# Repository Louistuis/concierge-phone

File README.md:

# Concierge phone

A small candybar phone you click and talk to. It sends your voice to an AI concierge in the cloud and talks back, and it carries a whole toolbox of radios and sensors the concierge can use.

**Status: paused, not built, not tested.** Board 1.3 is fully placed and passes every check except routing: the auto-router (Quilter) failed on all three runs, so the copper traces are not drawn yet. Treat everything here as an untested design. The cost to build 2 is in [pcb/QUOTE.md](pcb/QUOTE.md).

## What's inside

| | |
|---|---|
| Body | 54 x 108 x 15.5 mm, natural aluminium, black glass front |
| Brain | Waveshare ESP32-P4-Module (ESP32-P4 + ESP32-C6 for Wi-Fi 6 and Bluetooth LE) |
| Screen | 1.8" AMOLED with touch |
| Mobile data | Quectel EG915U-EU LTE Cat-1bis, nano-SIM |
| Location | u-blox MAX-M10S GNSS |
| Voice | 2 MEMS mics, MAX98357A amp + speaker, fingerprint Talk key |
| Camera | OV5647, 5 MP |
| Radios | NFC (ST25R3916B), sub-GHz (CC1101), LoRa (SX1262), IR receiver |
| Sensors | air quality (SGP41), colour (AS7341), distance (VL53L1), pressure (BMP581), temperature and humidity (SHT40), motion (ICM-42670), light (OPT3004), compass (MMC5603) |
| Feel | LRA haptics (DRV2605L), 3 side keys, privacy slide switch |
| Power | 2400 mAh LiPo, BQ24074 charger, BQ27441 fuel gauge, USB-C |
| Storage | microSD |
| Board | 50 x 102 mm, 6 layers, 1.0 mm, JLCPCB JLC06101H-3313 stackup |

The board is designed so it goes together with no soldering: the screen, battery, camera, fingerprint reader, antennas and speaker plug in or press onto spring contacts, and the rest is screws.

## How it's made

The whole board is generated by Python scripts that run inside KiCad 10. Nothing is drawn by hand, so every change is a script edit and a re-run.

```
pcb/sch_*.py        netlists for each block (core, power, rf, sense, ui), every part with its datasheet notes
pcb/gen_*.py        footprints KiCad doesn't ship
pcb/make_board.py   builds and places the board
pcb/fit_check.py    3D check that every part fits under the screen, battery and case
pcb/route.py        net classes, impedance widths, export for routing
pcb/quilter_prep.py input files for the Quilter auto-router
pcb/order_check.py  the order gate: DRC, nets, parts stock, fit; prints READY TO ORDER or NOT READY
enclosure/          Blender scripts for the concept renders
research/           part research notes
DESIGN.md           every design decision, in order, with the reasons
```

Run them with KiCad's own Python:

```
KPY=/Applications/KiCad/KiCad.app/Contents/Frameworks/Python.framework/Versions/Current/bin/python3
cd pcb
$KPY make_board.py
$KPY check_nets.py
$KPY export_view.py > shots/board.json
$KPY fit_check.py
$KPY route.py export
$KPY quilter_prep.py
$KPY order_check.py quilter/A-route-only/phone.kicad_pcb 5
```

## Not included

Manufacturer datasheets aren't in this repo; each part's notes in `pcb/sch_*.py` name the document and page they came from. The firmware isn't written yet.

## License

MIT, see [LICENSE](LICENSE). Use it, change it, build it. If you build one, say hi.

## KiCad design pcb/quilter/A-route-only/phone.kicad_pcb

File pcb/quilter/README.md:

# Quilter upload (made by pcb/quilter_prep.py, 2026-11-13)

Upload the **three files** of one folder (no zip): `phone.kicad_pro`, `phone.kicad_sch`, `phone.kicad_pcb`.

| Folder | What Quilter does |
|---|---|
| `B-place-and-route/` (try first) | Places 368 parts itself and routes. 71 parts stay where the case needs them (antennas, keys, connectors, module, modem, Talk ring, antenna feeds, test pads under the battery). Keep-outs stop parts landing under the battery, the fingerprint button, the camera head and the antenna band. |
| `A-route-only/` (backup) | Every part stays where make_board.py put it; Quilter only routes. Same parts, so it can be a second job in the same project. |

Both pass KiCad schematic parity (0 issues). Left-over DRC items are inside the parts' own footprints (mic sound holes, SIM tray NPTH, SW74 pads at the edge) or the deliberately tight antenna pi-match chains.

## Job settings
1. Stackup: JLCPCB 6-layer (or "from input file": In1 = gnd, In4 = pwr).
2. Differential pairs: CSI_* pairs **100 ohm**; USB_DP/DN, USB_HS_DP/DN, USB_JTAG_DP/DN **85 ohm** (USB wants 90, Quilter offers 85 or 100).
3. Single-ended impedance: add by net class **RF50**, 50 ohm.
4. Power nets: net class **Power** (auto-detected).
5. Preserved pours: none.

Free (Non-Commercial) tier: Quilter's terms allow training on what is uploaded. Projects expire.
Download the best candidate as KiCad and put it in `pcb/quilter/result/`; then run DRC, check_nets.py and jlc_files.py on it.

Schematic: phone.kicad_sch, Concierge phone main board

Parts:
AE30: 0868AT43A0020E; Johanson_0868AT43A0020; LCSC C3284550
AE31: W3011; Pulse_W3011; LCSC C6604735
C1, C395: 22uF; C_0805_2012Metric; LCSC C45783
C2, C20, C24, C103, C104, C105, C108, C109, C130, C348, C374, C390, C392, C701, C712, C719: 10uF; C_0603_1608Metric; LCSC C19702
C3, C8, C11, C12, C13, C14, C18, C22, C23, C25, C26, C27, C110, C117, C120, C122, C124, C126, C131, C300, C331, C339, C340, C341, C342, C343, C344, C345, C346, C347, C355, C369, C372, C373, C387, C388, C393, C394, C500, C501, C502, C503, C504, C508, C509, C510, C511, C512, C517, C518, C700, C702, C703, C704, C705, C706, C707, C708, C710, C713, C716, C720: 100nF; C_0201_0603Metric; LCSC C1525
C4, C7, C21, C101, C121, C123, C125, C127, C128, C313, C513, C514, C515, C516, C709, C711, C714, C715, C717, C718: 1uF; C_0402_1005Metric; LCSC C52923
C5, C6, C9, C10: DNP 33pF; C_0402_1005Metric; not fitted
C15, C16, C17, C19, C118, C315, C316: 33pF; C_0201_0603Metric; LCSC C1562
C100: 100nF 50V; C_0603_1608Metric; LCSC C14663
C102: 4.7uF 25V; C_0603_1608Metric; LCSC C69335
C106, C107: 22uF; C_0603_1608Metric; LCSC C59461
C111, C112, C113: 22uF 0805; C_0805_2012Metric; LCSC C45783
C114, C115, C116: 100uF; C_1210_3225Metric; LCSC C49066
C119: 10pF; C_0201_0603Metric; LCSC C32949
C129: 0.47uF; C_0402_1005Metric; LCSC C92361
C132, C302, C304, C306, C308, C310, C314, C506: 10nF; C_0201_0603Metric; LCSC C15195
C301, C305, C307, C309, C505, C507: 2.2uF; C_0402_1005Metric; LCSC C12530
C303, C391, C519: 4.7uF; C_0402_1005Metric; LCSC C23733
C311: 22nF; C_0201_0603Metric; LCSC C1532
C312, C351, C352, C386: 1nF; C_0201_0603Metric; LCSC C1523
C317, C324: 680pF; C_0402_1005Metric; LCSC C301953
C318, C325, C364: 100pF; C_0402_1005Metric; LCSC C1546
C319, C326: DNP 10pF; C_0402_1005Metric; not fitted
C320, C327: 82pF; C_0402_1005Metric; LCSC C45501
C321, C328: 56pF; C_0402_1005Metric; LCSC C1572
C322, C329: 10pF; C_0402_1005Metric; LCSC C1545
C323, C330: 180pF; C_0402_1005Metric; LCSC C97862
C332: 3.9nF C0G 50V; C_0603_1608Metric; LCSC C415537
C333: 150pF C0G 50V; C_0603_1608Metric; LCSC C1645
C334: DNP 220pF C0G 50V; C_0603_1608Metric; not fitted
C335, C357, C361: 220pF; C_0402_1005Metric; LCSC C39122
C336: 1nF C0G; C_0402_1005Metric; LCSC C53547
C337: 2.2nF C0G; C_0402_1005Metric; LCSC C385029
C338: 1nF C0G; C_0201_0603Metric; LCSC C53547
C349, C350: 15pF; C_0201_0603Metric; LCSC C1548
C353, C354: 100pF; C_0201_0603Metric; LCSC C1546
C356, C358: 3.9pF; C_0402_1005Metric; LCSC C1566
C359: 8.2pF; C_0402_1005Metric; LCSC C1579
C360: 5.6pF; C_0402_1005Metric; LCSC C1574
C362: 1.0pF; C_0402_1005Metric; LCSC C1550
C363, C365: 1.5pF; C_0402_1005Metric; LCSC C1552
C366: 3.3pF; C_0402_1005Metric; LCSC C1565
C367: 12pF; C_0402_1005Metric; LCSC C1547
C368: DNP 47pF; C_0402_1005Metric; not fitted
C370: DNP 3.9pF; C_0402_1005Metric; not fitted
C371: DNP 0.3pF; C_0402_1005Metric; not fitted
C375: 470nF; C_0402_1005Metric; LCSC C5137475
C376: 47nF; C_0201_0603Metric; LCSC C82219
C377: 82pF; C_0201_0603Metric; LCSC C45501
C378, C380: 6.8pF; C_0402_1005Metric; LCSC C1576
C379, C384: 2.4pF; C_0402_1005Metric; LCSC C48346
C381: 47pF; C_0402_1005Metric; LCSC C1567
C382: 2.7pF; C_0402_1005Metric; LCSC C1561
C383: 1.8pF; C_0402_1005Metric; LCSC C1553
C385, C397: DNP 1.0pF; C_0402_1005Metric; not fitted
C389: 10pF; C_0201_0603Metric; LCSC C1545
C396: DNP 2.2pF; C_0402_1005Metric; not fitted
D100: SMF15A; D_SOD-123F; LCSC C123802
D101: PTVSHC3D4V5U; D_SOD-323; LCSC C319211
D102: XL-3030UWC-1W-3V; LED_XINGLIGHT_XL-3030_3.0x3.0mm; LCSC C2843891
D300, D301, D302: BAT54WS; D_SOD-323; LCSC C124205
D303, D304: IR12-21C/TR8; Everlight_IR12-21C; LCSC C53672
D700, D701, D702, D703: XL-1615RGBC-RF; LED_XINGLIGHT_XL-1615RGBC_1.6x1.5mm; LCSC C965840
F100: 1206L200/24NR 2A 24V; Fuse_1206_3216Metric; LCSC C42396578
J1: AXE534127; Panasonic_AXE534127_A4S_34P; LCSC C6863072
J2: NANO SIM 7P H1.37; SIM_Nano_SHOUHAN_7P_H1.37; LCSC C7529384
J3: AFA07-S15FCA-00; JUSHUO_AFA07-S15FCA-00_1x15-1MP_P1.0mm_Horizontal; LCSC C262721
J4: TYPE-C-31-M-12; USB_C_Receptacle_HRO_TYPE-C-31-M-12; LCSC C165948
J5: U.FL-R-SMT-1(10) LTE; U.FL_Hirose_U.FL-R-SMT-1_Vertical; LCSC C88373
J6: U.FL-R-SMT-1(10) Wi-Fi; U.FL_Hirose_U.FL-R-SMT-1_Vertical; LCSC C88373
J10: S3B-PH-SM4-TB(LF)(SN); JST_PH_S3B-PH-SM4-TB_1x03-1MP_P2.00mm_Horizontal; LCSC C265101
J30, J35: BWCD-L5.5W2.0H3.0; Pogo_KTR47003_D2.0; LCSC C2826550
J31: 4308RV-404XJL; Coilcraft_4308RV
J32: TP CC_GDO2; TestPoint_Pad_D1.0mm
J33: TP GNSS_TP; TestPoint_Pad_D1.0mm
J34: TP GNSS_SAFEBOOT; TestPoint_Pad_D1.0mm
J70: Molex 53261-0671; Molex_PicoBlade_53261-0671_1x06-1MP_P1.25mm_Horizontal; LCSC C17393620
J71: 104031-0811; microSD_HC_Molex_104031-0811; LCSC C585350
L100: DFE201612E-R47M=P2 0.47uH 5.5A; L_Murata_DFE201610P; LCSC C668312
L101: XFL4020-152MEC 1.5uH; L_Coilcraft_XxL4020; LCSC C3033018
L300, L301: 270nH; L_0805_2012Metric; LCSC C162661
L302, L303, L305: 27nH; L_0402_1005Metric; LCSC C12669
L304: 22nH; L_0402_1005Metric; LCSC C12670
L306, L307, L310, L311: 12nH; L_0402_1005Metric; LCSC C77104
L308, L309: 18nH; L_0402_1005Metric; LCSC C86060
L312: DNP 3.3nH; L_0402_1005Metric; not fitted
L313: 15uH; L_0603_1608Metric; LCSC C486329
L314: 47nH; L_0402_1005Metric; LCSC C97998
L315: 2.2nH; L_0402_1005Metric; LCSC C86061
L316: 3.3nH; L_0402_1005Metric; LCSC C86064
L317: 10nH; L_0402_1005Metric; LCSC C77103
L318: 15nH; L_0402_1005Metric; LCSC C86059
L319: FB600; L_0402_1005Metric; LCSC C76884
LS70: Same Sky CMS-16093-078S; SPK_SPRING_PADS_2P_P2.4mm
M70: GT-BTP20002-0170B-020A (LRA VG0832009L); GSwitch_GT-BTP20002-0170B_2P_P2.0; LCSC C55079717
Q1: 2N7002; SOT-23; LCSC C8545
Q100, Q300, Q301: DMG1012T-7; SOT-523; LCSC C20512
R1, R4, R11, R12, R14, R16, R102, R105, R106, R113, R123, R124, R307, R500, R501, R507, R703, R707, R708, R709, R710, R712, R720, R722, R723, R724, R725, R726: 10k; R_0201_0603Metric; LCSC C25744
R2, R3: 2.2k; R_0201_0603Metric; LCSC C25879
R5, R6: 0; R_0201_0603Metric; LCSC C17168
R7, R8, R9: 22; R_0201_0603Metric; LCSC C25092
R10: 51k; R_0201_0603Metric; LCSC C25794
R13, R15: DNP 10k; R_0402_1005Metric; not fitted
R17, R18, R717, R718: 100; R_0201_0603Metric; LCSC C25076
R19: 15k; R_0201_0603Metric; LCSC C25756
R103: 1.18k; R_0402_1005Metric; LCSC C270651
R104: 887; R_0402_1005Metric; LCSC C474137
R107: 10k; R_0201_0603Metric
R108: 511k; R_0201_0603Metric; LCSC C64042
R109: 91k; R_0201_0603Metric; LCSC C4147
R110: 10; R_0201_0603Metric; LCSC C25077
R111: 1.2M; R_0201_0603Metric; LCSC C43675
R112: 180k; R_0201_0603Metric; LCSC C25760
R114: 60.4k; R_0201_0603Metric; LCSC C25911
R115, R117, R119, R121, R126, R127, R305, R308, R310, R312, R314, R316, R320, R324, R328, R502, R503, R504, R505, R700, R711, R713, R714, R716, R719: 100k; R_0201_0603Metric; LCSC C25741
R116, R120: 75k; R_0201_0603Metric; LCSC C25798
R118: 39k; R_0201_0603Metric; LCSC C25783
R122: 10mR 1% 0.5W; R_0805_2012Metric; LCSC C163089
R125: 910k; R_0201_0603Metric; LCSC C25800
R300, R301: 2.4R; R_0603_1608Metric; LCSC C22941
R302, R303: 68R; R_0402_1005Metric; LCSC C25131
R304, R327: 0R; R_0201_0603Metric; LCSC C17168
R306: 10k; R_0402_1005Metric; LCSC C25744
R309, R318, R323, R325: 100R; R_0201_0603Metric; LCSC C25076
R311: 56k; R_0201_0603Metric; LCSC C25796
R313, R315, R701, R702, R706: 1k; R_0201_0603Metric; LCSC C11702
R317, R326: 0R; R_0402_1005Metric; LCSC C17168
R319: 220R; R_0201_0603Metric; LCSC C25091
R321, R322: 47R; R_0603_1608Metric; LCSC C23182
R506: 4.7; R_0201_0603Metric; LCSC C137962
R704, R705: 0 DNP; R_0402_1005Metric
R715: 33; R_0201_0603Metric; LCSC C25105
R721: 100k DNP; R_0402_1005Metric
SW70: 4 mm metal snap dome; SnapDome_4mm
SW71, SW72, SW73: EVQPUB02K; Panasonic_EVQPUK_EVQPUB; LCSC C2915192
SW74: SSSS811101; SW_SPDT_PCM12; LCSC C109335
TP1: TP BOOT; TestPoint_Pad_D1.0mm
TP2: TP EN; TestPoint_Pad_D1.0mm
TP3: TP U0TXD; TestPoint_Pad_D1.0mm
TP4: TP U0RXD; TestPoint_Pad_D1.0mm
TP5: TP GND; TestPoint_Pad_D1.0mm
TP6: TP C6_U0RXD; TestPoint_Pad_D1.0mm
TP7: TP C6_U0TXD; TestPoint_Pad_D1.0mm
TP8: TP C6_IO9; TestPoint_Pad_D1.0mm
TP9: TP LTE_USB_VBUS; TestPoint_Pad_D1.0mm
TP10: TP LTE_USB_DP; TestPoint_Pad_D1.0mm
TP11: TP LTE_USB_DM; TestPoint_Pad_D1.0mm
TP12: TP LTE_USB_BOOT; TestPoint_Pad_D1.0mm
TP13: TP LTE_DBG_TX; TestPoint_Pad_D1.0mm
TP14: TP LTE_DBG_RX; TestPoint_Pad_D1.0mm
TP15: TP 1V8_LTE; TestPoint_Pad_D1.0mm
TP100: VBUS; TestPoint_Pad_D1.0mm
TP101: VBAT; TestPoint_Pad_D1.0mm
TP102: VSYS; TestPoint_Pad_D1.0mm
TP103: 3V3; TestPoint_Pad_D1.0mm
TP104: 3V8_LTE; TestPoint_Pad_D1.0mm
TP105: GND; TestPoint_Pad_D1.0mm
TP106: LS_FAULT; TestPoint_Pad_D1.0mm
U1: Waveshare ESP32-P4-Module (28101); Waveshare_ESP32-P4-Module
U2: EG915UEUAC-N05-SNNSA; Quectel_EG915U; LCSC C7471302
U3, U4: SN74AXC4T774PWR; TSSOP-16_4.4x5mm_P0.65mm; LCSC C1849453
U5, U6: TS3USB221ARSER; Texas_UQFN-10_1.5x2mm_P0.5mm; LCSC C128396
U7: TPD4E05U06DQAR; USON-10_2.5x1.0mm_P0.5mm; LCSC C2827646
U10: TPS63802DLAR; TI_DLA_VSON-HR-10_2x3mm; LCSC C2845237
U11: BQ24074RGTR; VQFN-16-1EP_3x3mm_P0.5mm_EP1.68x1.68mm; LCSC C54313
U12: TPS63020DSJR; DFN-14-1EP_3x4mm_P0.5mm_EP1.7x3.3mm; LCSC C15483
U13: BQ27441DRZT-G1A; TI_DRZ0012A_VSON-12_2.5x4mm; LCSC C2864880
U14, U15, U16, U17, U76: AP22653AW6-7; SOT-23-6; LCSC C1511768
U18: LM36011YKBR; TI_YKB0008_DSBGA-8_0.8x1.5mm_P0.35mm; LCSC C213547
U19: TPD6S300ARUKR; Texas_RUK0020B_WQFN-20-1EP_3x3mm_P0.4mm_EP1.7x1.7mm; LCSC C2876380
U20: TUSB320LAIRWBR; Texas_X2QFN-12_1.6x1.6mm_P0.4mm; LCSC C132554
U30: ST25R3916B-AQET; QFN-32-1EP_5x5mm_P0.5mm_EP3.45x3.45mm; LCSC C17315217
U31: CC1101RGPR; Texas_RGP0020H_VQFN-20-1EP_4x4mm_P0.5mm_EP2.4x2.4mm; LCSC C29953
U32: SX1262IMLTRT; QFN-24-1EP_4x4mm_P0.5mm_EP2.7x2.7mm; LCSC C191341
U33: MAX-M10S-00B; ublox_MAX; LCSC C4153167
U34, U70: SN74LVC2G34DCKR; SOT-363_SC-70-6; LCSC C14461
U35: TLV7011DCKR; SOT-353_SC-70-5; LCSC C193688
U36: TSOP57338TT1; Vishay_TSOP57xxx_3.95x3.95mm; LCSC C3742877
U37, U38, U39, U40, U41: PE4259-63; SOT-363_SC-70-6; LCSC C470892
U42: DNP SAFFB1G56KB0F0A; Filter_1109-5_1.1x0.9mm; not fitted
U50: PCAL6524HEAZ; HVQFN-32-1EP_5x5mm_P0.5mm_EP3.1x3.1mm; LCSC C3000497
U51: PI4IOE5V6408ZTAEX; UQFN-16_1.8x2.6mm_P0.4mm; LCSC C526717
U52: ICM-42670-P; LGA-14_3x2.5mm_P0.5mm_LayoutBorder3x4y; LCSC C3288646
U53: MMC5603NJ; MEMSIC_WLP-4_0.8x0.8mm_P0.4mm; LCSC C404328
U54: BMP581; Bosch_BMP581_LGA-10_2x2mm_P0.5mm; LCSC C5362283
U55: SHT40-AD1B-R3; Sensirion_DFN-4_1.5x1.5mm_P0.8mm_SHT4x_NoCentralPad; LCSC C2848306
U56: OPT3004DNPR; TI_DNP0006A_USON-6-1EP_2x2mm_P0.65mm_EP0.65x1.35mm; LCSC C2655153
U57: AS7341-DLGM; AMS_OLGA-8_2x3.1mm_P0.8mm; LCSC C2649486
U58: XC6206P182MR; SOT-23; LCSC C21659
U59: SGP41-D-R4; Sensirion_DFN-6-1EP_2.44x2.44mm_P0.8mm_SGP4x; LCSC C3659325
U60: ATECC608B-MAHDA-S; DFN-8-1EP_3x2mm_P0.5mm_EP1.3x1.5mm; LCSC C1518773
U61: VL53L1CXV0FY/1; ST_VL53L1x; LCSC C190004
U71, U72: IM73D122V01XTMA1; Infineon_PG-LLGA-5-2; LCSC C5563886
U73: MAX98357AETE+T; TQFN-16-1EP_3x3mm_P0.5mm_EP1.23x1.23mm; LCSC C910544
U74: DRV2605LDGSR; MSOP-10_3x3mm_P0.5mm; LCSC C527464
U75: LP5815DRLR; SOT-583-8; LCSC C47262831
Y30: 27.12MHz X32252712MSB4SI; Crystal_SMD_3225-4Pin_3.2x2.5mm; LCSC C70591
Y31: 26MHz X322526MMB4SI; Crystal_SMD_3225-4Pin_3.2x2.5mm; LCSC C15192
Y32: TCXO 32MHz 1.8V TG2520SMN; Oscillator_SMD_SeikoEpson_TG2520SMN-xxx-xxxxxx-4Pin_2.5x2.0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; LCSC C7527388

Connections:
1V8_LTE: C7.1, C8.1, C12.1, C14.1, R10.2, TP15.1, U2.29 (VDD_EXT), U3.15 (1V8_LTE), U4.15 (1V8_LTE)
1V8_SPEC: C512.1, C514.1, U57.1 (1V8_SPEC), U58.2 (1V8_SPEC)
3V3: C1.1, C2.1, C3.1, C11.1, C13.1, C23.1, C26.1, C27.1, C101.1, C106.1, C107.1, C120.1, C122.1, C124.1, C126.1, C131.1, C392.1, C393.1, C394.1, C500.1, C501.1, C502.1, C503.1, C504.1, C505.1, C506.1, C507.1, C508.1, C509.1, C510.1, C511.1, C513.1, C516.1, C517.1, C518.1, C519.1, C700.1, C715.1, C716.1, C717.1, D302.2 (3V3), J1.16 (TP_VCC), R1.1, R2.2, R3.2, R4.2, R102.2, R105.2, R106.2, R108.1, R124.2, R126.2, R127.2, R500.2, R501.2, R504.2, R506.1, R507.2, R705.1, R707.2, R708.2, R709.2, R710.2, SW74.2 (3V3), TP103.1, U1.84 (VBAT), U1.85 (ESP_3V3), U1.86 (ESP_3V3), U3.1 (3V3), U3.2 (3V3), U3.16 (3V3), U4.1 (3V3), U4.16 (3V3), U5.10 (3V3), U6.10 (3V3), U10.6 (VOUT), U14.1 (3V3), U15.1 (3V3), U16.1 (3V3), U17.1 (3V3), U19.10 (3V3), U20.12 (3V3), U33.7 (3V3), U33.8 (3V3), U50.27 (3V3), U50.31 (3V3), U51.2 (3V3), U51.15 (3V3), U52.1 (3V3), U52.5 (3V3), U52.8 (3V3), U52.12 (3V3), U53.B1 (VDD), U54.1 (VDDIO), U54.6 (CSB), U54.10 (VDD), U55.3 (3V3), U56.1 (VDD), U56.2 (ADDR), U58.3 (3V3), U59.5 (VDDH), U60.8 (3V3), U61.1 (3V3), U61.11 (3V3), U74.5 (3V3), U74.6 (3V3), U74.10 (3V3), U75.4 (3V3), U76.1 (3V3)
3V8_LTE: C111.1, C112.1, C113.1, C114.1, C115.1, C116.1, C117.1, C118.1, C119.1, D101.1 (3V8_LTE), R111.1, TP104.1, U2.32 (VBAT_BB), U2.33 (VBAT_BB), U2.52 (VBAT_RF), U2.53 (VBAT_RF), U12.4 (3V8_LTE), U12.5 (3V8_LTE)
AMP_BCLK: U1.24 (GPIO9), U73.16 (AMP_BCLK)
AMP_DIN: U1.27 (GPIO12), U73.1 (AMP_DIN)
AMP_GAIN: R721.1, U73.2 (AMP_GAIN)
AMP_SD: R720.1, U50.12 (AMP_SD)
AMP_SDMODE: R720.2, U73.4 (AMP_SDMODE)
AMP_WS: U1.25 (GPIO10), U73.14 (AMP_WS)
ANT_SUBG_FEED: AE30.1 (FEED), C371.1, R317.2
BAT_NTC: J10.2 (BAT_NTC), R107.1, U11.1 (BAT_NTC)
BOOT: TP1.1, U1.62 (GPIO35)
C6_IO9: TP8.1, U1.9 (C6_IO9)
C6_U0RXD: TP6.1, U1.4 (C6_U0RXD)
C6_U0TXD: TP7.1, U1.5 (C6_U0TXD)
CAM_3V3: C24.1, C25.1, C123.1, J3.15 (CAM_3V3), R16.2, U15.6 (CAM_3V3)
CAM_EN: R714.1, U50.7 (CAM_EN), U70.3 (CAM_EN)
CAM_EN_SW: R117.1, U15.3 (CAM_EN_SW), U70.4 (CAM_EN_SW)
CAM_IO0: J3.11 (CAM_IO0), R16.1
CC1_P: U19.12 (CC1_P), U20.1 (CC1_P)
CC2_P: U19.11 (CC2_P), U20.2 (CC2_P)
CC433_B: C357.1, L302.2
CC433_F1: C359.1, L304.2, L305.1
CC433_F2: C360.1, C361.1, L305.2
CC433_N: C358.1, L303.1, U38.1 (CC433_N)
CC433_OUT: C361.2, U39.1 (CC433_OUT)
CC433_P: C356.1, L302.1, U37.1 (CC433_P)
CC433_X: C356.2, L303.2, L304.1
CC868_A: C362.1, C365.1, L306.2, L309.1
CC868_B: C362.2, C363.1, L307.2, L308.1
CC868_C: C364.1, L309.2
CC868_F: C366.1, L310.2, L311.1
CC868_G: C367.1, C368.1, L311.2
CC868_H: C368.2, L312.1
CC868_N: L307.1, U38.3 (CC868_N)
CC868_OUT: C367.2, L312.2, U39.3 (CC868_OUT)
CC868_P: L306.1, U37.3 (CC868_P)
CC868_X: C365.2, L308.2, L310.1
CC_CS: R312.1, U1.79 (GPIO51), U31.7 (CC_CS)
CC_DCOUPL: C342.1, U31.5 (CC_DCOUPL)
CC_GDO0: U1.81 (GPIO53), U31.6 (CC_GDO0)
CC_GDO2: J32.1, U31.3 (CC_GDO2)
CC_RBIAS: R311.1, U31.17 (CC_RBIAS)
CC_RFN: C354.1, U31.13 (CC_RFN)
CC_RFN_SW: C354.2, U38.5 (CC_RFN_SW)
CC_RFP: C353.1, U31.12 (CC_RFP)
CC_RFP_SW: C353.2, U37.5 (CC_RFP_SW)
CC_XOSC1: C349.1, U31.8 (CC_XOSC1), Y31.1 (CC_XOSC1)
CC_XOSC2: C350.1, U31.10 (CC_XOSC2), Y31.3 (CC_XOSC2)
CHG_EN1: Q100.1 (CHG_EN1), R126.1, U11.6 (CHG_EN1), U20.7 (CHG_EN1)
CHG_EN2: C132.1, Q100.3 (CHG_EN2), R127.1, U11.5 (CHG_EN2)
CHG_N: R105.1, U11.9 (CHG_N), U51.12 (CHG_N)
CSI_CLKN: J3.8 (CSI_CLKN), U1.44 (CSI_CLKN)
CSI_CLKP: J3.9 (CSI_CLKP), U1.43 (CSI_CLKP)
CSI_D0N: J3.2 (CSI_D0N), U1.41 (CSI_D0N)
CSI_D0P: J3.3 (CSI_D0P), U1.42 (CSI_D0P)
CSI_D1N: J3.5 (CSI_D1N), U1.45 (CSI_D1N)
CSI_D1P: J3.6 (CSI_D1P), U1.46 (CSI_D1P)
DISP_3V3: C20.1, C21.1, C22.1, C121.1, J1.18 (VBAT), J1.20 (VBAT), J1.24 (VCI), J1.26 (VDDIO), R11.2, R12.2, R14.2, U14.6 (DISP_3V3)
DISP_EN: R115.1, U14.3 (DISP_EN), U50.8 (DISP_EN)
DISP_IM0: J1.19 (IM0), R12.1, R13.1
DISP_IM1: J1.17 (IM1), R14.1, R15.1
DISP_PWR_EN: J1.22 (PWR_EN), R11.1
DRV_REG: C714.1, U74.1 (DRV_REG)
EN: C4.1, R1.2, TP2.1, U1.87 (CHIP_PU)
EXP_INT: R4.1, U1.17 (GPIO2), U50.32 (EXP_INT), U51.1 (EXP_INT), U56.5 (INT), U57.7 (EXP_INT)
EXP_RST_N: R500.1, U50.28 (EXP_RST_N), U51.10 (EXP_RST_N)
FB_3V3: R108.2, R109.1, U10.4 (FB)
FB_LTE: R111.2, R112.1, U12.3 (FB_LTE)
FP_3V3: C701.1, C702.1, J70.1 (FP_3V3), R703.1, R705.2, U76.6 (FP_3V3)
FP_EN: R505.1, R704.1, U50.24 (FP_EN), U76.3 (FP_EN)
FP_MOD_RX: J70.3 (FP_MOD_RX), R701.2
FP_MOD_TX: J70.4 (FP_MOD_TX), R702.1
FP_MOD_WAKE: J70.6 (FP_MOD_WAKE), R706.1
FP_RST: J70.5 (FP_RST), R703.2, R704.2
FP_RX: R702.2, U1.19 (GPIO4)
FP_TOUCH: R706.2, U51.4 (FP_TOUCH)
FP_TX: R701.1, U1.18 (GPIO3)
FUEL_ALRT: R124.1, U13.12 (GPOUT), U51.5 (FUEL_ALRT)
GAUGE_BIN: R123.1, U13.10 (BIN)
GAUGE_VDD: C129.1, U13.5 (VDD)
GND: AE31.2 (GND), C1.2, C2.2, C3.2, C4.2, C5.2, C6.2, C7.2, C8.2, C9.2, C10.2, C11.2, C12.2, C13.2, C14.2, C15.2, C16.2, C17.2, C18.2, C19.2, C20.2, C21.2, C22.2, C23.2, C24.2, C25.2, C26.2, C27.2, C100.2, C101.2, C102.2, C103.2, C104.2, C105.2, C106.2, C107.2, C108.2, C109.2, C110.2, C111.2, C112.2, C113.2, C114.2, C115.2, C116.2, C117.2, C118.2, C119.2, C120.2, C121.2, C122.2, C123.2, C124.2, C125.2, C126.2, C127.2, C128.2, C129.2, C130.2, C131.2, C132.2, C300.2, C301.2, C302.2, C303.2, C304.2, C305.2, C306.2, C307.2, C308.2, C309.2, C310.2, C311.2, C312.2, C313.2, C314.2, C315.2, C316.2, C317.2, C320.2, C321.2, C323.2, C324.2, C327.2, C328.2, C330.2, C331.2, C336.2, C337.2, C338.2, C339.2, C340.2, C341.2, C342.2, C343.2, C344.2, C345.2, C346.2, C347.2, C348.2, C349.2, C350.2, C351.2, C352.2, C355.2, C357.2, C358.2, C359.2, C360.2, C363.2, C364.2, C366.2, C369.2, C370.2, C371.2, C372.2, C373.2, C374.2, C375.2, C376.2, C377.2, C378.2, C380.2, C382.2, C383.2, C385.2, C386.2, C387.2, C388.2, C390.2, C391.2, C392.2, C393.2, C394.2, C395.2, C396.2, C397.2, C500.2, C501.2, C502.2, C503.2, C504.2, C505.2, C506.2, C507.2, C508.2, C509.2, C510.2, C511.2, C512.2, C513.2, C514.2, C515.2, C516.2, C517.2, C518.2, C519.2, C700.2, C701.2, C702.2, C703.2, C704.2, C705.2, C706.2, C707.2, C708.2, C709.2, C710.2, C711.2, C712.2, C713.2, C714.2, C715.2, C716.2, C717.2, C718.2, C719.2, C720.2, D100.2 (GND), D101.2 (GND), D102.1 (K), J1.3 (GND(DCX)), J1.4 (GND), J1.21 (GND), J1.23 (MIPI_CLKP(GND)), J1.25 (MIPI_CLKN(GND)), J1.27 (GND), J1.28 (GND), J1.29 (MIPI_D0P(GND)), J1.31 (MIPI_D0N(GND)), J1.33 (GND), J1.MP (GND), J2.8 (SHELL_GND), J2.9 (SHELL_GND), J2.10 (SHELL_GND), J2.11 (SHELL_GND), J2.C5 (GND), J3.1 (GND), J3.4 (GND), J3.7 (GND), J3.10 (GND), J3.MP (GND), J4.A1 (GND), J4.A12 (GND), J4.B1 (GND), J4.B12 (GND), J4.SH (GND), J5.2 (GND), J6.2 (GND), J10.3 (GND), J70.2 (GND), J71.6 (GND), J71.10 (GND), J71.SH (GND), Q1.2 (GND), Q100.2 (GND), Q300.2 (GND), Q301.2 (GND), R13.2, R15.2, R103.2, R104.2, R107.2, R109.2, R112.2, R113.2, R114.2, R115.2, R116.2, R117.2, R118.2, R119.2, R120.2, R121.2, R123.2, R304.2, R305.2, R306.2, R310.2, R311.2, R314.2, R316.2, R324.2, R502.2, R503.2, R505.2, R700.2, R711.2, R713.2, R714.2, R716.2, R719.2, R721.2, SW70.2 (GND), SW71.2 (GND), SW72.2 (GND), SW73.2 (GND), TP5.1, TP105.1, U1.1 (GND), U1.3 (GND), U1.15 (GND), U1.33 (GND), U1.40 (GND), U1.47 (GND), U1.52 (GND), U1.83 (GND), U2.3 (GND), U2.31 (GND), U2.47 (USIM1_GND), U2.48 (GND), U2.50 (GND), U2.54 (GND), U2.55 (GND), U2.58 (GND), U2.59 (GND), U2.61 (GND), U2.62 (GND), U2.67 (GND), U2.68 (GND), U2.69 (GND), U2.70 (GND), U2.71 (GND), U2.72 (GND), U2.73 (GND), U2.74 (GND), U2.79 (GND), U2.80 (GND), U2.81 (GND), U2.82 (GND), U2.89 (GND), U2.90 (GND), U2.91 (GND), U2.100 (GND), U2.101 (GND), U2.102 (GND), U3.7 (GND), U3.8 (GND), U3.10 (GND), U4.2 (GND), U4.4 (GND), U4.7 (GND), U4.8 (GND), U4.10 (GND), U4.13 (GND), U5.5 (GND), U5.6 (GND), U6.5 (GND), U6.9 (GND), U7.3 (GND), U7.8 (GND), U10.2 (MODE), U10.3 (AGND), U10.8 (GND), U11.4 (GND), U11.8 (GND), U11.17 (GND), U12.2 (GND), U12.13 (GND), U12.15 (GND), U13.3 (VSS), U13.13 (EP), U14.2 (GND), U15.2 (GND), U16.2 (GND), U17.2 (GND), U18.A1 (GND), U18.B2 (GND), U19.8 (GND), U19.13 (GND), U19.16 (GND), U19.17 (GND), U19.18 (GND), U19.21 (GND), U20.3 (GND), U20.10 (GND), U20.11 (GND), U30.6 (GND), U30.12 (GND), U30.16 (GND), U30.20 (GND), U30.21 (GND), U30.26 (GND), U30.33 (GND), U31.16 (GND), U31.19 (GND), U31.21 (GND), U32.2 (GND), U32.5 (GND), U32.8 (GND), U32.20 (GND), U32.25 (GND), U33.1 (GND), U33.10 (GND), U33.12 (GND), U34.2 (GND), U35.2 (GND), U36.6 (GND), U36.8 (GND), U37.2 (GND), U38.2 (GND), U39.2 (GND), U40.2 (GND), U41.2 (GND), U42.2 (GND), U42.3 (GND), U42.5 (GND), U50.25 (GND), U50.26 (GND), U50.33 (GND), U51.9 (GND), U51.16 (GND), U52.6 (GND), U52.7 (GND), U53.A1 (VSA), U54.3 (VSS), U54.5 (SDO), U54.7 (INT), U54.8 (VSS), U54.9 (VSS), U55.4 (GND), U56.3 (GND), U56.7 (EP), U57.3 (GND), U57.5 (GND), U58.1 (GND), U59.2 (VSS), U59.4 (NA_GND), U59.7 (DIE_PAD), U60.4 (GND), U60.9 (GND), U61.2 (GND), U61.3 (GND), U61.4 (GND), U61.6 (GND), U61.12 (GND), U70.2 (GND), U71.4 (GND), U71.5 (GND), U72.5 (GND), U73.3 (GND), U73.11 (GND), U73.15 (GND), U73.17 (GND), U74.4 (GND), U74.8 (GND), U75.3 (GND), U75.5 (GND), U76.2 (GND), Y30.2 (GND), Y30.4 (GND), Y31.2 (GND), Y31.4 (GND), Y32.2 (GND)
GNSS_ANT: AE31.1 (GNSS_ANT), C396.1, R326.1
GNSS_RF_IN: R327.2, U33.11 (GNSS_RF_IN), U42.4 (GNSS_RF_IN)
GNSS_RST: U33.9 (GNSS_RST), U51.8 (GNSS_RST)
GNSS_SAFEBOOT: J34.1, U33.18 (GNSS_SAFEBOOT)
GNSS_SAW_IN: C397.1, R326.2, R327.1, U42.1 (GNSS_SAW_IN)
GNSS_TP: J33.1, U33.4 (GNSS_TP)
GNSS_VBCKP: C395.1, D302.1 (GNSS_VBCKP), U33.6 (GNSS_VBCKP)
I2C_SCL: J1.8 (TP_SCL), J3.13 (I2C_SCL), R3.1, U1.23 (GPIO8), U13.2 (SCL), U18.D2 (I2C_SCL), U33.17 (I2C_SCL), U50.29 (I2C_SCL), U51.13 (I2C_SCL), U52.13 (I2C_SCL), U53.A2 (SCL), U54.2 (SCK), U55.2 (I2C_SCL), U56.4 (SCL), U57.2 (I2C_SCL), U59.6 (SCL), U60.6 (I2C_SCL), U61.10 (I2C_SCL), U74.2 (I2C_SCL), U75.1 (I2C_SCL)
I2C_SDA: J1.10 (TP_SDA), J3.14 (I2C_SDA), R2.1, U1.22 (GPIO7), U13.1 (SDA), U18.C2 (I2C_SDA), U33.16 (I2C_SDA), U50.30 (I2C_SDA), U51.14 (I2C_SDA), U52.14 (I2C_SDA), U53.B2 (SDA), U54.4 (SDI), U55.1 (I2C_SDA), U56.6 (SDA), U57.8 (I2C_SDA), U59.3 (SDA), U60.5 (I2C_SDA), U61.9 (I2C_SDA), U74.3 (I2C_SDA), U75.2 (I2C_SDA)
ILIM_CAM: R116.1, U15.5 (ILIM_CAM)
ILIM_CHG: R103.1, U11.12 (ILIM_CHG)
ILIM_DISP: R114.1, U14.5 (ILIM_DISP)
ILIM_FP: R700.1, U76.5 (ILIM_FP)
ILIM_RF: R118.1, U16.5 (ILIM_RF)
ILIM_SD: R120.1, U17.5 (ILIM_SD)
IMU_INT: U50.15 (IMU_INT), U52.4 (IMU_INT)
IR_A1: D303.1 (A), R321.2
IR_A2: D304.1 (A), R322.2
IR_K: D303.2 (K), D304.2 (K), Q301.3 (IR_K)
IR_RX: U1.29 (GPIO20), U36.1 (IR_RX)
IR_TX: R323.1, U1.70 (GPIO42)
IR_TX_G: Q301.1 (IR_TX_G), R323.2, R324.1
IR_VCC: C391.1, R325.2, U36.5 (IR_VCC)
ISET_CHG: R104.1, U11.16 (ISET_CHG)
LCD_CS: J1.11 (LCD_CS), U1.55 (GPIO28)
LCD_RST: J1.1 (LCD_RESET), J1.14 (TP_RESET), U50.13 (LCD_RST)
LCD_TE: J1.2 (TE), U1.54 (GPIO27)
LF_CARRIER: U1.68 (GPIO40), U34.1 (LF_CARRIER), U34.3 (LF_CARRIER)
LF_COIL1: C332.2, C333.2, C334.2, C335.1, D301.2 (LF_COIL1), J31.1
LF_COIL2: J31.2, R304.1
LF_DATA: U1.53 (GPIO26), U35.1 (LF_DATA)
LF_DRV: C332.1, C333.1, C334.1, R302.2, R303.2
LF_DRV1: R302.1, U34.6 (LF_DRV1)
LF_DRV2: R303.1, U34.4 (LF_DRV2)
LF_ENV: C337.1, D300.1 (LF_ENV), R306.1, R307.1
LF_FILT: C338.1, R307.2, R308.1, U35.3 (LF_FILT)
LF_LM: D301.1 (LF_LM), Q300.3 (LF_LM)
LF_PULL: R309.1, U1.69 (GPIO41)
LF_PULL_G: Q300.1 (LF_PULL_G), R309.2, R310.1
LF_REF: C339.1, R308.2, U35.4 (LF_REF)
LF_TAP: C335.2, C336.1, D300.2 (LF_TAP), R305.1
LORA_BUSY: U32.14 (LORA_BUSY), U50.20 (LORA_BUSY)
LORA_CS: R320.1, U1.76 (GPIO48), U32.19 (LORA_CS)
LORA_DCC: L313.1, U32.9 (LORA_DCC)
LORA_DIO1: U1.20 (GPIO5), U32.13 (LORA_DIO1)
LORA_DIO2: R318.1, U32.12 (LORA_DIO2)
LORA_DIO2_F: C386.1, R318.2, U41.4 (LORA_DIO2_F)
LORA_DIO3: L319.1, U32.6 (LORA_DIO3)
LORA_PA: C378.1, C379.1, L314.2, L315.2, L316.1
LORA_RF: U40.3 (LORA_RF), U41.5 (LORA_RF)
LORA_RFIN: C384.1, L318.1, U32.22 (LORA_RFIN)
LORA_RFIP: C383.1, L318.2, U32.21 (LORA_RFIP)
LORA_RFO: L315.1, U32.23 (LORA_RFO)
LORA_RST: U32.15 (LORA_RST), U50.21 (LORA_RST)
LORA_RX: C384.2, C385.1, U41.3 (LORA_RX)
LORA_TCXO_AC: C389.2, R319.1
LORA_TCXO_OUT: C389.1, Y32.3 (LORA_TCXO_OUT)
LORA_TCXO_VCC: C388.1, L319.2, Y32.4 (LORA_TCXO_VCC)
LORA_TX: C382.1, L317.2, U41.1 (LORA_TX)
LORA_TX1: C379.2, C380.1, C381.1, L316.2
LORA_TX2: C381.2, L317.1
LORA_VREG: C375.1, L313.2, U32.7 (LORA_VREG)
LORA_VRPA: C376.1, C377.1, L314.1, U32.24 (LORA_VRPA)
LORA_XTA: R319.2, U32.3 (LORA_XTA)
LRA_N: M70.2 (LRA_N), U74.9 (LRA_N)
LRA_P: M70.1 (LRA_P), U74.7 (LRA_P)
LS_FAULT: R102.1, TP106.1, U14.4 (LS_FAULT), U15.4 (LS_FAULT), U16.4 (LS_FAULT), U17.4 (LS_FAULT), U19.9 (LS_FAULT), U76.4 (LS_FAULT)
LTE_ANT: C10.1, J5.1 (LTE_ANT), R6.2
LTE_CTS_3V: U1.77 (GPIO49), U3.6 (LTE_CTS_3V)
LTE_DBG_RX: TP14.1, U2.22 (DBG_RXD)
LTE_DBG_TX: TP13.1, U2.23 (DBG_TXD)
LTE_DTR_3V: U4.3 (LTE_DTR_3V), U50.3 (LTE_DTR_3V)
LTE_EN: R113.1, U12.12 (LTE_EN), U50.1 (LTE_EN)
LTE_OE_N: R501.1, U3.9 (LTE_OE_N), U4.9 (LTE_OE_N), U50.4 (LTE_OE_N)
LTE_PWRKEY: Q1.1 (LTE_PWRKEY), R502.1, U50.2 (LTE_PWRKEY)
LTE_RF: C9.1, R6.1, U2.60 (ANT_MAIN)
LTE_RI_3V: U4.5 (LTE_RI_3V), U50.6 (LTE_RI_3V)
LTE_RTS_3V: U1.32 (GPIO23), U3.4 (LTE_RTS_3V)
LTE_RXD_3V: U1.31 (GPIO22), U3.5 (LTE_RXD_3V)
LTE_STATUS_3V: U4.6 (LTE_STATUS_3V), U50.5 (LTE_STATUS_3V)
LTE_TXD_3V: U1.30 (GPIO21), U3.3 (LTE_TXD_3V)
LTE_USB_BOOT: TP12.1, U2.75 (USB_BOOT)
LTE_USB_DM: TP11.1, U2.10 (USB_DM)
LTE_USB_DP: TP10.1, U2.9 (USB_DP)
LTE_USB_VBUS: TP9.1, U2.8 (USB_VBUS)
MIC1_DATA: R717.1, U71.1 (MIC1_DATA)
MIC2_DATA: R718.1, U72.1 (MIC2_DATA)
MIC_3V3: C707.1, C708.1, C709.1, C710.1, C711.1, R711.1, R712.1, SW74.1 (MIC_3V3), U70.5 (MIC_3V3), U71.2 (MIC_3V3), U72.2 (MIC_3V3), U72.4 (MIC_3V3)
MIC_CLK: R713.1, U1.26 (GPIO11), U70.1 (MIC_CLK)
MIC_CLK_B: R715.1, U70.6 (MIC_CLK_B)
MIC_CLK_G: R715.2, R716.1, U71.3 (MIC_CLK_G), U72.3 (MIC_CLK_G)
MIC_DATA: R717.2, R718.2, R719.1, U1.28 (GPIO13)
M_CTS: U2.36 (MAIN_CTS), U3.11 (M_CTS)
M_DTR: U2.30 (MAIN_DTR), U4.14 (M_DTR)
M_PWRKEY_N: Q1.3 (M_PWRKEY_N), U2.15 (PWRKEY)
M_RI: U2.39 (MAIN_RI), U4.12 (M_RI)
M_RTS: U2.37 (MAIN_RTS), U3.13 (M_RTS)
M_RXD: U2.34 (MAIN_RXD), U3.14 (M_RXD)
M_STATUS: U2.20 (STATUS), U4.11 (M_STATUS)
M_TXD: U2.35 (MAIN_TXD), U3.12 (M_TXD)
NFC_AGD: C313.1, C314.1, U30.24 (NFC_AGD)
NFC_ANT1: J30.1, R300.2
NFC_ANT2: J35.1, R301.2
NFC_CS: R328.1, U1.78 (GPIO50), U30.29 (NFC_CS)
NFC_EMI1: C317.1, C318.1, C319.1, L300.2
NFC_EMI2: C324.1, C325.1, C326.1, L301.2
NFC_IRQ: U1.80 (GPIO52), U30.27 (NFC_IRQ)
NFC_M1: C318.2, C319.2, C320.1, C321.1, C322.1, R300.1
NFC_M2: C325.2, C326.2, C327.1, C328.1, C329.1, R301.1
NFC_RFI1: C322.2, C323.1, U30.22 (NFC_RFI1)
NFC_RFI2: C329.2, C330.1, U30.23 (NFC_RFI2)
NFC_RFO1: L300.1, U30.13 (NFC_RFO1)
NFC_RFO2: L301.1, U30.15 (NFC_RFO2)
NFC_VDD_A: C307.1, C308.1, U30.7 (NFC_VDD_A)
NFC_VDD_AM: C311.1, C312.1, U30.11 (NFC_VDD_AM)
NFC_VDD_D: C305.1, C306.1, U30.3 (NFC_VDD_D)
NFC_VDD_RF: C309.1, C310.1, U30.9 (NFC_VDD_RF), U30.14 (NFC_VDD_RF)
NFC_XTI: C315.1, U30.5 (NFC_XTI), Y30.1 (NFC_XTI)
NFC_XTO: C316.1, U30.4 (NFC_XTO), Y30.3 (NFC_XTO)
PGOOD_N: R106.1, U11.7 (PGOOD_N), U51.11 (PGOOD_N)
PRIV_STATE: R712.2, U51.3 (PRIV_STATE)
QSPI_CLK: J1.9 (QSPI_CLK), U1.57 (GPIO30)
QSPI_D0: J1.5 (QSPI_D0), U1.56 (GPIO29)
QSPI_D1: J1.7 (QSPI_D1), U1.58 (GPIO31)
QSPI_D2: J1.13 (QSPI_D2), U1.60 (GPIO33)
QSPI_D3: J1.15 (QSPI_D3), U1.59 (GPIO32)
RF_3V3: C125.1, C300.1, C301.1, C302.1, C303.1, C304.1, C331.1, C340.1, C341.1, C343.1, C344.1, C345.1, C346.1, C347.1, C348.1, C355.1, C369.1, C372.1, C373.1, C374.1, C387.1, R312.2, R320.2, R325.1, R328.2, U16.6 (RF_3V3), U30.1 (RF_3V3), U30.8 (RF_3V3), U30.10 (RF_3V3), U31.4 (RF_3V3), U31.9 (RF_3V3), U31.11 (RF_3V3), U31.14 (RF_3V3), U31.15 (RF_3V3), U31.18 (RF_3V3), U32.1 (RF_3V3), U32.10 (RF_3V3), U32.11 (RF_3V3), U34.5 (RF_3V3), U35.5 (RF_3V3), U37.6 (RF_3V3), U38.6 (RF_3V3), U39.6 (RF_3V3), U40.6 (RF_3V3), U41.6 (RF_3V3)
RF_ANT_SUBG: C370.1, R317.1, U40.5 (RF_ANT_SUBG)
RF_BAND: R313.1, U50.18 (RF_BAND)
RF_BAND_F: C351.1, R313.2, R314.1, U37.4 (RF_BAND_F), U38.4 (RF_BAND_F), U39.4 (RF_BAND_F)
RF_EN: R119.1, U16.3 (RF_EN), U50.9 (RF_EN)
RF_RADIO: R315.1, U50.19 (RF_RADIO)
RF_RADIO_F: C352.1, R315.2, R316.1, U40.4 (RF_RADIO_F)
RF_SUBGHZ: U39.5 (RF_SUBGHZ), U40.1 (RF_SUBGHZ)
RING_B: D700.4 (B), D701.4 (B), D702.4 (B), D703.4 (B), U75.6 (RING_B)
RING_G: D700.3 (G), D701.3 (G), D702.3 (G), D703.3 (G), U75.7 (RING_G)
RING_R: D700.1 (R), D701.1 (R), D702.1 (R), D703.1 (R), U75.8 (RING_R)
SBU1: J4.A8 (SBU1), U19.1 (SBU1)
SBU1_P: U6.8 (SBU1_P), U19.15 (SBU1_P)
SBU2: J4.B8 (SBU2), U19.2 (SBU2)
SBU2_P: U6.7 (SBU2_P), U19.14 (SBU2_P)
SBU_OE_N: R504.1, U6.6 (SBU_OE_N), U50.17 (SBU_OE_N)
SBU_RX: R18.2, U6.2 (SBU_RX)
SBU_TX: R17.2, U6.1 (SBU_TX)
SD_3V3: C127.1, C719.1, C720.1, J71.4 (SD_3V3), R722.2, R723.2, R724.2, R725.2, R726.2, U17.6 (SD_3V3)
SD_CD: J71.9 (SD_CD), U50.11 (SD_CD)
SD_CLK: J71.5 (SD_CLK), U1.71 (GPIO43)
SD_CMD: J71.3 (SD_CMD), R722.1, U1.72 (GPIO44)
SD_D0: J71.7 (SD_D0), R723.1, U1.67 (GPIO39)
SD_D1: J71.8 (SD_D1), R724.1
SD_D2: J71.1 (SD_D2), R725.1
SD_D3: J71.2 (SD_D3), R726.1
SD_EN: R121.1, U17.3 (SD_EN), U50.10 (SD_EN)
SGP_VDD: C515.1, R506.2, U59.1 (VDD)
SIDE_KEY: C704.1, R708.1, SW71.1 (SIDE_KEY), U1.16 (GPIO1)
SIM_CLK: C16.1, J2.C3 (CLK), R8.2, U7.2 (SIM_CLK)
SIM_DATA: C17.1, J2.C7 (I/O), R9.2, R19.2, U7.1 (SIM_DATA)
SIM_RST: C15.1, J2.C2 (RST), R7.2, U7.4 (SIM_RST)
SPI_MISO: U1.75 (GPIO47), U30.32 (SPI_MISO), U31.2 (SPI_MISO), U32.16 (SPI_MISO)
SPI_MOSI: U1.74 (GPIO46), U30.31 (SPI_MOSI), U31.20 (SPI_MOSI), U32.17 (SPI_MOSI)
SPI_SCK: U1.73 (GPIO45), U30.30 (SPI_SCK), U31.1 (SPI_SCK), U32.18 (SPI_SCK)
SPK_N: LS70.2 (-), U73.10 (SPK_N)
SPK_P: LS70.1 (+), U73.9 (SPK_P)
SW1_3V3: L100.1, U10.9 (L1)
SW1_LTE: L101.1, U12.8 (SW1_LTE), U12.9 (SW1_LTE)
SW2_3V3: L100.2, U10.7 (L2)
SW2_LTE: L101.2, U12.6 (SW2_LTE), U12.7 (SW2_LTE)
TALK_SW: C703.1, R707.1, SW70.1 (TALK_SW), U1.88 (GPIO0)
TOF_INT: R507.1, U51.6 (TOF_INT), U61.7 (TOF_INT)
TOF_XSHUT: U51.7 (TOF_XSHUT), U61.5 (TOF_XSHUT)
TORCH_LED: D102.2 (A), U18.D1 (TORCH_LED)
TPD_VBIAS: C100.1, U19.3 (TPD_VBIAS)
TP_INT: J1.12 (TP_INT), U50.14 (TP_INT)
U0RXD: R18.1, TP4.1, U1.65 (GPIO38)
U0TXD: R17.1, TP3.1, U1.64 (GPIO37)
USB_CC1: J4.A5 (USB_CC1), U19.4 (USB_CC1), U19.7 (USB_CC1)
USB_CC2: J4.B5 (USB_CC2), U19.5 (USB_CC2), U19.6 (USB_CC2)
USB_DN: J4.A7 (USB_DN), J4.B7 (USB_DN), U5.7 (USB_DN), U19.19 (USB_DN)
USB_DP: J4.A6 (USB_DP), J4.B6 (USB_DP), U5.8 (USB_DP), U19.20 (USB_DP)
USB_HS_DN: U1.48 (USB_HS_DM), U5.4 (USB_HS_DN)
USB_HS_DP: U1.49 (USB_HS_DP), U5.3 (USB_HS_DP)
USB_JTAG_DN: U1.50 (GPIO24), U5.2 (USB_JTAG_DN)
USB_JTAG_DP: U1.51 (GPIO25), U5.1 (USB_JTAG_DP)
USB_SEL: R503.1, U5.9 (USB_SEL), U50.16 (USB_SEL)
USIM_CLK: R8.1, U2.46 (USIM1_CLK)
USIM_DATA: R9.1, U2.45 (USIM1_DATA)
USIM_DET: J2.CD (CD_SW), R10.1, U2.42 (USIM1_DET)
USIM_RST: R7.1, U2.44 (USIM1_RST)
USIM_VDD: C18.1, C19.1, J2.C1 (VCC), R19.1, U2.43 (USIM1_VDD), U7.5 (USIM_VDD)
VBAT: C104.1, C108.1, C109.1, C130.1, C390.1, R110.1, R122.2, R321.1, R322.1, TP101.1, U11.2 (VBAT), U11.3 (VBAT), U12.10 (VBAT), U12.11 (VBAT), U13.7 (SRN), U18.A2 (VBAT), U18.C1 (VBAT)
VBAT_PACK: C128.1, J10.1 (VBAT_PACK), R122.1, U13.6 (BAT), U13.8 (SRP)
VBUS: C102.1, D100.1 (VBUS), F100.2 (VBUS), R125.1, TP100.1, U11.13 (VBUS)
VBUS_CONN: F100.1 (VBUS_CONN), J4.A4 (VBUS_CONN), J4.A9 (VBUS_CONN), J4.B4 (VBUS_CONN), J4.B9 (VBUS_CONN)
VBUS_DET: R125.2, U20.4 (VBUS_DET)
VINA_LTE: C110.1, R110.2, U12.1 (VINA_LTE)
VOL_DN: C706.1, R710.1, SW73.1 (VOL_DN), U50.23 (VOL_DN)
VOL_UP: C705.1, R709.1, SW72.1 (VOL_UP), U50.22 (VOL_UP)
VSYS: C103.1, C105.1, C712.1, C713.1, C718.1, D700.2 (A), D701.2 (A), D702.2 (A), D703.2 (A), TP102.1, U10.1 (EN), U10.10 (VIN), U11.10 (VSYS), U11.11 (VSYS), U73.7 (VSYS), U73.8 (VSYS)
WIFI_ANT: C6.1, J6.1 (WIFI_ANT), R5.2
WIFI_RF: C5.1, R5.1, U1.2 (LNA_OUT)

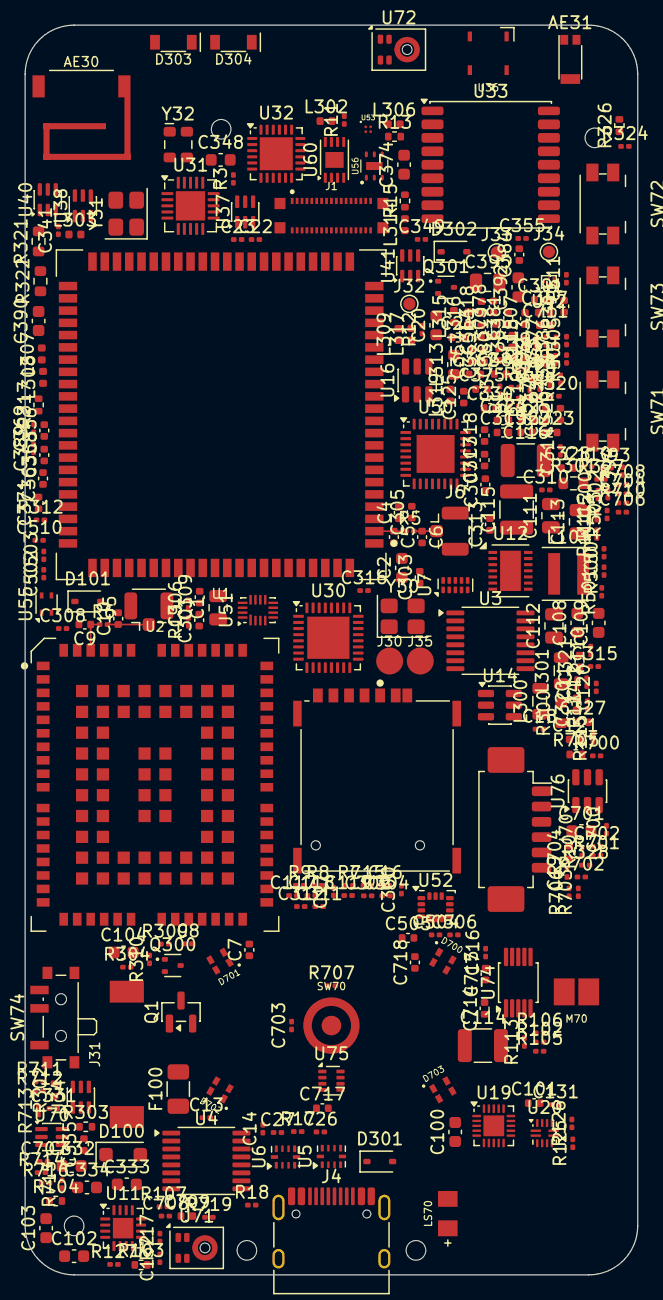
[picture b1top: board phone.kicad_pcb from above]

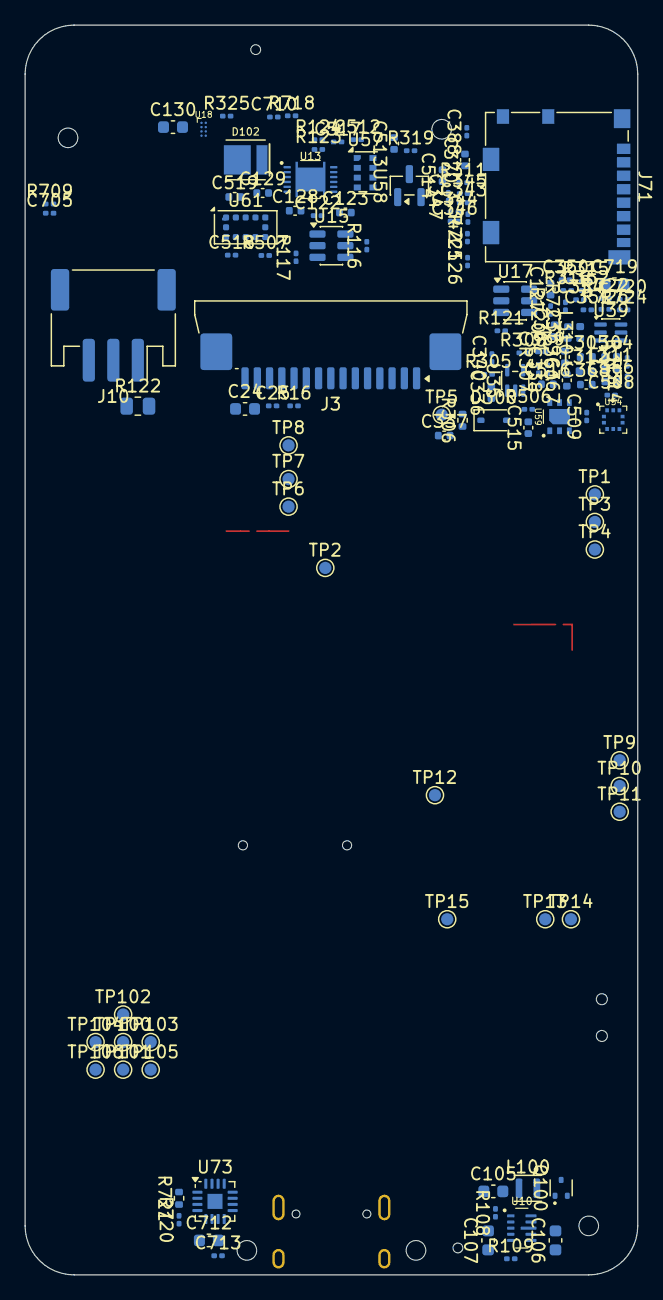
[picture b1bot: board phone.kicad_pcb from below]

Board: 6 copper layers, 50.0 x 102.0 mm, 451 parts (130 on the bottom side), 283 nets.

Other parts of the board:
H1, H2, H3, H4, H5: M1.4 screw; MountingHole_M1.4_NPTH
